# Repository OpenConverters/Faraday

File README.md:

# Faraday

**Automated EMC design review for PCB layouts — in your browser, your board never leaves your machine.**

Faraday loads a PCB layout, screens the whole board with computational geometry + closed-form
transmission-line physics, and returns a **ranked list of crosstalk and EMC risk findings** —
each with the mechanism, the number, a stated confidence tier, and a remediation hint.

## Guided and advanced

One switch in the header, and it is the same review either way — same engine, same
findings, same ranking. **Guided** says each finding in the language of the person who
drew the board (*"this track crosses a gap in the copper underneath it, so its return
current has to detour"* · *"route around the gap, close it, or bridge it with a
capacitor"*), replaces the emissions sliders with four converter presets whose
assumptions are printed rather than hidden, and answers in words. **Advanced** is
everything: decibels, frequencies, confidence tiers, the physics text and the sliders
that drive it. Nothing is suppressed in guided and nothing is softened — the vocabulary
is the only difference, and every number is one click away (panels carry the switch too,
since the header sits behind them). A first visit lands in guided; the choice is
remembered.

## Formats

| Format | Reaches | Notes |
|---|---|---|
| **KiCad** `.kicad_pcb` | KiCad 5–9 | legacy layer names, `(module)`, zone-inherited fills |
| **HyperLynx** `.hyp` | Altium, PADS, Expedition, Eagle | carries its own stackup with permittivity |
| **IPC-2581** `.xml` | rev B/C exporters | no other open-source reader exists |
| **ODB++** job | Altium, Cadence, Mentor, KiCad 9 | exact nets, refdes and values; a directory or one zip |
| **Gerber X2** set | anything that fabs | net attributes where present; all files or one zip |
| **Gerber + IPC-D-356** | Altium fab outputs, TI EVM/TIDA zips | classic RS-274X named by Protel extensions; the .ipc netlist supplies exact nets, refdes and pins, propagated through the copper |

Format is detected from the file's **contents**, not its name. Native CAD
databases are not read — an Altium `.PcbDoc` is a binary OLE file; export
ODB++ (or Gerber X2) from it and drop that. Neither carries a dielectric, so
Faraday reads the layer count off the board and asks only what it is built on.

## Rules

`coupled-run` (edge, broadside, and to copper-pour boundaries) · `diff-pair` (intentional
coupling, never a defect) · `3w` · `plane-crossing` and `sparse-reference` (return-path breaks,
rolled up when systemic) · `via-stub` and `dangling-stub` (λ/4 resonators) ·
`decoupling-distance` · and for power converters, `switch-node` and **`commutation-loop`** —
the input-cap → switch-pair → return loop whose enclosed area dominates converter emissions.
Six rules implement Franz (*EMV: Störungssicherer Aufbau elektronischer Schaltungen*, 5th ed.):
`connector-ground-spread` (scattered cable-ground entries drive the cables as antennas, §7.2),
`plane-cavity-mode` (VCC/GND cavity resonances from Gl. 5.3, corner vs. centre excitation, §5.9.3),
`cap-via-stub` (decoupling-branch stub inductance, §5.6), `critical-mesh-ground` (the
commutation loop crossing a ground-domain boundary, §8.17.1 — via his Stromumschaltanalyse on
the netlist derived from the layout), `pdn-antiresonance` (mixed-value decoupling's parallel
resonance, computed from the PDN branch model, §5.5/§5.9.5) and `edge-radiation`
(switch-node copper at the board edge).

A recognised **line filter** gets its own three: `filter-io-coupling` (the dirty and
clean sides routed together — a path *around* the filter that caps its insertion loss no
matter what the parts do), `y-cap-return` (the Y capacitor's own mounting inductance, and
the frequency above which it stops being a capacitor) and `filter-bypass` (switching
copper beside the connector side, re-injecting behind the filter). The block is found by
shape — a four-pad wound part whose pads split two-and-two into four distinct non-return
nets, with at least one X or Y capacitor on them — so a flyback transformer is never
mistaken for a filter.

**Immunity** is one mechanism, and it is pure layout: `esd-clamp-distance` and
`esd-clamp-return` turn the copper between a connector pin and its clamp — and the clamp's
own path to the plane — into the volts they actually are (`V = L·di/dt`, ~30 A/ns for an
IEC 61000-4-2 contact discharge, ~0.8 nH/mm), and `esd-unprotected-pin` states, at info
grade, which connector pins reach silicon with no clamp near them. Whether a pin needs one
is a product decision, so that last one is coverage, never a verdict. Pads carry their pin names through every importer,
so conduction paths are derivable, not guessed.

The derived meshes are validated against a real-board corpus — vendor-documented EVM hot
loops, human-reviewed member sets, format-determinism pins. The full ledger (stats,
wrong-member cases found and fixed, format coverage) lives in
[corpus/README.md](corpus/README.md).

Monolithic converters (switcher IC + inductor, no discrete FET) surface as **candidate**
switch nodes: the evidence is shown in the meta strip and one click screens the net
(recorded as user-declared in the report). They are never screened automatically, because a
linear regulator followed by an LC filter presents the identical external netlist — measured,
not assumed. A net with a capacitor straight to the return is never a switch node at all:
the cap would short the switch every cycle.

Faraday is an automated **design review**, not compliance prediction. Screening-tier numbers are
first-order estimates for *ranking* risk; a field-solver tier (OMFEM 2D cross-section RLGC +
in-process ngspice via Kirchhoff) refines selected pairs.

## Layout

- `cpp/include/faraday/` — header-only C++20 core (s-expr parser, board IR, KiCad importer,
  transmission-line closed forms, screening engine)
- `cpp/tests/` — Catch2 tests (run the binary directly, never ctest)
- `cpp/tools/` — `faraday_cli`: `.kicad_pcb` → `report.json` + console summary
- `web/` — Vite + Vue GUI: drop a board, rendered layout with severity overlays, hover tooltips,
  two-way-linked findings list. The engine runs in WASM — nothing is uploaded.
- `scripts/build_wasm.sh` — emsdk build of the WASM engine into `web/public/`

## Build (native)

```sh
cmake -S cpp -B build -DCMAKE_BUILD_TYPE=Release
cmake --build build -j
./build/test_faraday        # Catch2 (run the binary directly, never ctest)
./build/faraday_cli board.kicad_pcb -o report.json
./build/faraday_cli board.hyp
./build/faraday_cli board.xml --stackup default-4layer
```

## The bench — field solve and transient, in the browser

Any coupled-run finding offers **Solve this cross-section**. That opens a 2D
boundary-element extraction of the actual geometry and a transient of the coupled pair,
both running in the page:

- the **field** of the real cross-section, computed in closed form from the panel charges
  (no mesh, and the reference plane is exact by images rather than truncated);
- **RLGC** — Z₀, Z even/odd, ε_eff, delay, mutual L and C, backward coupling;
- the **victim's noise waveform**, NEXT and FEXT, against its receiver's threshold;
- a **verdict in millivolts** against the DC input margin of a named logic family, and
  the separation that would bring it back under budget.

Extraction plus transient is a few milliseconds, so the sliders — separation, edge rate,
coupled length, swing — re-solve the physics as they move. See
[docs/browser-field-tier.md](docs/browser-field-tier.md) for the formulation, the
validation table, and the modelling limits.

## Radiated emissions — does it pass?

On a converter, `commutation-loop` findings offer **Predict radiated emissions →**. The
enclosed loop area comes off the copper — the one input every other estimator makes you
measure by hand — and the panel puts the resulting spectrum against the **CISPR 32 /
EN 55032** or **FCC Part 15** limit line, with a margin in dB.

Sliders for switched current, switching frequency, edge rate and duty; the plateau above
the edge knee is set by loop area, current and edge rate alone, so halving any one of
them buys exactly 6 dB.

The same panel carries the **common-mode budget**: how much common-mode current an
attached cable of a given length may carry and still pass. Faraday cannot predict your
actual common-mode current — it comes from ground-plane impedance and return-path
detours, not from geometry — but the inverse needs no unknowns, and it lands in
*microamps*, which is why an ordinary current probe never sees the mechanism that fails
most products.

### Conducted — which mode, at what frequency, and how many dB

Below 30 MHz nothing radiates off a board this size; it walks out on the wires, and it
walks out as **two different problems that need two different components**. The panel
drives the same trapezoid into the two paths a LISN measures — differential mode through
the input capacitor's branch impedance, common mode through the stray capacitance to
earth — and judges **both against the conducted limit line, here**: CISPR 32 / EN 55032
Class A or B mains, quasi-peak or average, the same values Hertz carries and pinned
against them by test. What comes back is the sentence the estimate is worth: *"39 dB over
the limit at 0.5 MHz, and it is common-mode noise"*, with the frequency above which it
stays common mode, and the attenuation each stage has to find at the design frequency
(ANP015's `A_req = level − limit + 10 dB`). A common-mode problem and a differential-mode
problem are fixed by different parts, so which one you have is the first question, not a
footnote.

**The input capacitors are the board's own.** The differential-mode path *is* the input
branch's impedance, and that branch is on the layout: the commutation loop already names
the capacitor that supplies the current step, so its rail is the branch, and every
capacitor across it joins in — with the **mounting inductance measured pad-to-via** on
your copper, not a datasheet ESL. It is carried as a network rather than a lumped value,
because the bulk sets C, the ceramics set L, and their crossover is a real feature of the
curve. (Fixing this found a parser bug worth its own line: `390µF` was being silently
skipped, because the micro sign is not ASCII — three of the five capacitors on the MPPT's
own input rail.)

**Limit lines**: CISPR 32 / EN 55032 mains, Class A and B, quasi-peak and average — and
**CISPR 25** conducted, classes 1–5, for automotive. CISPR 25 only regulates protected
broadcast bands, so between them there is no limit and the verdict says exactly that
instead of scoring against a zero; when the switching fundamental lands in a gap, no
attenuation figure is quoted at all. The DM model is written against the 50 µH/100 Ω mains
network, and against an automotive line the panel says so rather than quietly reading the
wrong LISN.

**C_stray is derived, not invented.** The plate that turns dV/dt into common-mode current
is the switching copper, and Faraday measures it off the layout the same way it measures
the commutation loop — tracks, pads and pours on every switch net, summed. What a layout
file cannot carry is how far the metalwork is, so that is the only thing left to ask:
a gap in millimetres, and whether the board is spaced off the chassis (air) or bolted
against it (through the laminate, 4.5×). Fringing only adds, so the figure is a stated
floor on the geometry's contribution — a heatsink on the device tab, a transformer's
inter-winding capacitance and the harness add paths no layout can see.

**The operating point can come from the design.** Switched current, switching frequency,
edge rate and bus voltage are circuit properties no layout carries — so Faraday takes them
from whatever designed the converter: `#op=<base64 json>` in the URL fragment (the reverse
direction of the Hertz bridge, private for the same reason), range-checked at the door and
credited in the meta strip. Without one, guided mode offers four converter presets and
prints the numbers behind the choice.

Then **design the filter that fixes this →** hands the two mode spectra to
[Hertz](https://hertz.openconverters.com) in the URL *fragment* — the part of a URL that
never reaches any server — where the CM and DM stages get sized against real parts and
the filter's own PCB can be generated. Levels are peak against a quasi-peak line, which
errs pessimistic; DM ±10 dB, CM ±15 dB. It seeds a filter design before hardware exists.
It does not replace a LISN.

The loop figure is an **estimate**, and the panel says so where it cannot be missed: differential-mode
loop radiation only, no common-mode current on attached cables (which dominates most real
failures), no enclosure, no board resonances. A clean result means this loop is not your
problem — not that the product passes.

## The SPICE deck — what the copper adds, where a simulator can read it

A conducted-emissions prediction needs two halves. A circuit simulation knows
the devices and nothing about the copper; Faraday measures the copper and cannot
know the devices. `--spice` writes Faraday's half:

```bash
faraday_cli board.kicad_pcb --stackup default-4layer \
    --spice deck.cir --manifest deck.json --chassis-gap-mm 8
```

The subcircuit is five ports — the rail as it *arrives*, the rail *after* the
mesh inductance (where the switching cell attaches), the switch node, the return
and chassis — and between them the parasitics, each measured: the commutation
mesh's inductance (Grover over the derived loop hull, ~15% against FastHenry),
the input capacitor bank part by part with **mounting inductance measured
pad-to-via**, and the stray capacitance from the dv/dt copper area to a stated
chassis gap. It is topology-neutral on purpose: Faraday measures copper, it does
not decide that a board is a buck.

The manifest gives every value a **provenance** — `measured` off the copper,
`derived` from measured quantities, `stated` by you, or `default` (a model
constant, named as such: ESR is the only one, and for an electrolytic it is
optimistic). A deck whose reader cannot tell which is which gets trusted
uniformly, and most of it should not be.

And the file **names its own absences** at the top, before anything a machine
reads: no device models, no gate loop, no control loop, nothing off the board.
It is deliberately not runnable alone — a deck that omitted those silently would
look runnable and produce numbers with the authority of a simulation and the
content of a guess. `faraday_spice_check` (built when Kirchhoff is available)
wraps it in a harness and solves an operating point through Kirchhoff's
**in-process libngspice**, so "it parses" is a fact and not a hope.

Boards that cannot answer say so: no switch node, no derived commutation loop,
or a stackup that does not fit gets a sentence and an exit code, never an empty
deck. This is stage 1 of ABT #804 — the pipeline that ends in a simulated CM/DM
spectrum judged against a limit line.

## The whole conducted pipeline — a board in, a CM/DM verdict out

The deck above is stage 1 of four (ABT #804). End to end, on your own machine,
nothing uploaded:

```bash
# 1. the device, from the parts catalogue — or a refusal
kelvin-spice-model --catalog mosfets.ndjson --part EPC2019 --name SW --out q.lib

# 2. the board's parasitics + that device + a LISN, run to steady state
faraday_emi_sim board.kicad_pcb --stackup default-4layer --chassis-gap-mm 8 \
    --model q.lib --vin 48 --duty 0.4 --fsw 500e3 --iload 10 --out emi.json

# 3. read it the way a receiver does, and judge it
python3 hertz/scripts/read_simulated.py emi.json --limit cispr32b --out spectra.json
```

```
 DM  worst   -32.3 dB at   2.000 MHz   (level 88.3 dBuV, needs 42 dB …)
 CM  worst    -3.6 dB at   2.000 MHz   (level 59.6 dBuV, needs 14 dB …)
dominant   : DM — that is the stage to design first
```

Each repo owns its half: **Kelvin** the device model and its *tier* (vendor /
datasheet-parameterised / refused — never a class default, which is
indistinguishable from a real model once it is in a netlist), **Faraday** the
parasitics and the assembly, **Kirchhoff** the in-process libngspice, **Hertz**
the LISN, the CM/DM separation and the limit lines. Nothing is duplicated.

`spectra.json` loads straight back into the emissions panel, where the
simulated curves are drawn **beside** the analytic trapezoid seed rather than
replacing it, with the gap between them stated at the seed's worst frequency.
On the MPPT the two independent paths ask for 14 dB of CM attenuation each and
42 vs 50 dB of DM — inside the seed's own ±10 dB band, which is the first
evidence either path has that the other is not wrong.

What it still is not: **validated**. A simulated spectrum with a limit line on
it looks like a compliance prediction, and this project earns those claims
(FastHenry for loop inductance, vendor hot loops for the derived mesh, nine
boards for cross-format agreement). ABT #810 is that instrument —
`hertz/scripts/compare_measured.py` reports the error per decade against a real
LISN measurement — and it is open, waiting on lab data rather than on code.

## The return-path layer

The **return path** chip colours every trace by its *effective loop height* — how far
away its return current really is, in millimetres. The regime is high frequency, where
the return concentrates directly under the trace: the dielectric height where the plane
is genuinely there (checked against the actual pour polygons), the lateral detour around
a slot edge where it is not, and the hop to the nearest spanning stitching via at every
layer change.

Every number in this layer is a **geometric fact of the layout** — no assumed currents,
no field units, no dB. It replaced a "radiation attribution" whose ranking turned out to
be 97% a restatement of the switch-node rule once measured; the defensible far-field
number lives in the emissions panel, which has a limit line to check it against.

## The component near-field map

The **near field** chip opens a different regime from the radiation layer. At component
scale below ~1 GHz, `k·r ≪ 1` and the fields *are* the magnetostatic dipole fields:
decay is **1/r³ — 18 dB per doubling**, not 6, and E and H are independent (wave
impedance spans five orders of magnitude at 5 mm, so the far-field `+51.5 dB` conversion
is wrong by ±40–55 dB there).

It shows |H| in A/m at a stated probe height, and for each sensitive component the
voltage induced in its own loop against the threshold for its class — a precision
current-sense amp is judged at 15 µV, a 12-bit ADC at 806 µV.

**This is why some components get shielded**, and the answer has two halves that are
routinely conflated. A thin conductive can is excellent against a *voltage-driven*
E-field source (reflection dominates; the bond to ground is the limit, not the metal)
and **nearly useless against a low-frequency magnetic near field** — single-digit dB
below ~10 MHz regardless of material. A magnetically shielded inductor is not shielded
by a can at all; it has a closed magnetic path.

It renders as a heat wash **on the board itself**, with the copper drawn over it, and
**victims & shielding →** opens the per-part table plus a shield-can model. That model
shows the thing a datasheet usually hides: at 130 MHz a 0.2 mm wall absorbs ~950 dB and
only the **cover-to-frame contact pitch** matters, while at 500 kHz the wall binds
instead and tin-plated steel beats brass by ~49 dB. Same can, opposite lever.

It carries no dBµV/m, no limit line and no pass/fail: there is no reliable near-field to
far-field transform. See [docs/near-field-map-design.md](docs/near-field-map-design.md).

## The parts — click one, read the datasheet, get a cross-reference

Every component is drawn on the board as a body over its pads (the IR carries no
courtyard, so a part is a black box in the literal sense: the union of its pads and
a margin), with its reference on it once there is room. The **parts** chip turns the
layer off. Hovering says reference, value, footprint, pin count and side; **clicking
opens the part inspector**, which is what a PCB explorer shows and then what only this
one can:

- **On the board**: every pin and the net it is on, the layer, the placement, and the
  review's findings that touch the part's nets — one click jumps to the finding.
- **In the catalogue** — [Kelvin](https://kelvin.openconverters.com), the OpenConverters
  parts librarian, read *in the browser* (same-origin shards, one record per HTTP Range
  read; the board never leaves the machine). A part number on the board is looked up as
  an exact string, and the inspector says which catalogue families it searched and
  whether the hit was exact or a substring. The record comes back with the
  manufacturer's own **datasheet link**, the headline specs, every curve the datasheet
  carries, and the flattened spec sheet. When the export carried a part number and no
  value (Altium's ODB++), the record's value can be **adopted onto the board** in one
  click, so the PDN and the conducted models get the capacitance they refuse to guess.
- **No part number?** A KiCad board says `100n` in a `C_0603` — a value, not a part. The
  inspector matches the value (inside an E-series step) and the package read off the
  footprint name against the catalogue and lists what fits, stating how many value
  matches it scanned, how many carry no case code, and how many sit in another package.
  Pick one and it becomes the original for the record and the cross-reference.
- **Cross-references**: Kelvin's own deterministic ranker (the C++ `CrossRef` behind
  kelvin.openconverters.com, imported from the sibling checkout — never a second
  implementation) scores every candidate from the manufacturers you mark against the
  original's datasheet numbers: per-parameter pass/warn/fail, a grade (drop-in · minor
  review · major review · redesign · no substitute), the direction (upgrade/downgrade),
  physical fit, mount type, AEC-Q grade and lifecycle. Default question: *any other
  manufacturer*. When the original's own gating parameter is not in the catalogue, no
  candidate can grade better than partial, and the table says so.

A refdes prefix is a convention, not a contract — ANSI, DIN and IEC disagree on what
`T`, `Q` and `L` mean — so prefixes only *order* the families searched; the footprint
name and the value's unit letter weigh in first, and the remaining families are one
click away with the download cost stated. A verdict is a catalogue comparison, not a
qualification: read both datasheets.

**Does it fit? The measured body answers, not the case string.** A catalogue case code
is genuinely ambiguous and vendors disagree: Murata ships 1.0 × 0.5 mm capacitors whose
case field reads `0603` — the *metric* code for what everyone else calls an imperial
0402. Read as an imperial code that part gets offered as fitting a 1.6 mm land it is
0.6 mm too short for. So where a record carries a mechanical drawing, the part's own
length and width decide the fit (orientation-agnostic, ±12% per axis, which is wide
enough for a real 0603 body at 1.60 ±0.15 and narrow enough that neighbours stay
distinct on both axes); the case code answers only where no drawing exists, and the
panel says which one spoke. Non-chip packages (TO-220, SOT-23, a can) keep the code
check: those are families of drawings with real variation, not one standard rectangle.

### The catalogue overlay — which of these parts can I actually source?

The **in catalogue** chip asks the catalogue about *every* part on the board at once
and recolours the parts layer by the answer: green identified by part number, amber
candidates to choose from, red nothing in the catalogue fits, and grey **the board never
named it** — a part the export described with neither a number nor a value, which is a
gap in the export and not a hole in the catalogue, so it gets its own colour rather than
being counted as a miss. Work is grouped by catalogue family so each family downloads
once, progress is reported as it goes, and a second click stops it and keeps what was
answered. On the MPPT demo board: 139 parts, 2 identified, 91 with candidates, 33
unmatched, 13 the board never named.

### When the catalogue has never heard of it

A part number the catalogue cannot resolve is a dead end the inspector can get out of:
**look it up at the distributor** hands the part number to
[Heaviside](https://heaviside.openconverters.com)'s librarian, which searches the
distributor, converts the result into the same catalogue record shape, schema-validates
it, and **stages it for the catalogue**. What comes back renders with exactly the code
that renders a catalogue record — the vendor's datasheet link, the specs, the curves.

Three outcomes, kept distinct on purpose, because a caller acts on them: the part was
found and staged; the distributor answered and has no such part; or **the distributor
could not be asked** (credentials, transport, rate limit). The third is never dressed as
the second — a reader told "this part does not exist" would go and enter it by hand.

Nothing here writes to the catalogue. A found part lands in Heaviside's `staging/`, a
librarian applies it into TAS, and the next index build is what puts it in front of you.
A web button is not a way around that review. Only the part *number* leaves the browser;
it is a public string printed on the component, and the layout stays where it always
was.

Serving: the engine (`/kelvin.js`) and the data set (`/kelvin/*`) are same-origin — the
CSP allows nothing else. Prod nginx serves Kelvin's deployed bundle and the box's shared
`/cache/kelvin` (`ops/faraday.nginx`); the dev server proxies both from the live Kelvin
site, so a local board talks to the real catalogue. Kelvin's web sources are imported at
build time from `../../Kelvin/web/src` (`KELVIN_WEB_SRC` to override).

## PDN impedance — measured off the board

The **pdn** chip turns every decoupling capacitor into a series R-L-C branch whose
inductance is **measured off the layout** — pad-to-via escape on each terminal plus the
barrels — and plots the rail's |Z| against a target derived from your transient current
and allowed ripple, with its anti-resonance peaks marked. A cap whose mounting
inductance exceeds its ESL is wasted by placement, not by choice of part, and this is
the view that shows it.

## Also in the box

- **Impedance calculator** (from the start screen, no board needed): a real 2D
  boundary-element solve of the cross-section — Z₀, Z_diff, ε_eff, delay — plus a width
  finder that bisects to a target impedance.
- **Report export**: one self-contained HTML file of the whole review, with the
  screening caveats attached to it rather than left behind.
- **Bench sweep**: peak victim noise against separation as a curve, with the budget
  line, not one point at a time.
- **Copper loss**: the bench's transient now carries skin-effect R at the edge's knee
  frequency, so unterminated ringing is damped the amount real copper damps it.
- **Diff-pair skew**: recognized pairs are checked for intra-pair length mismatch —
  skew converts differential signal into the common mode that reaches the cable.
- Near-field victims carry a **cos θ from their own routed direction**, capacitive
  broadside overlaps over switch copper get their divider-ceiling bound, and inductors
  on switch nets are sources with a stated construction derating.

## Formats — what is and is not supported

| format | status |
|---|---|
| KiCad `.kicad_pcb` (v5–v9) | ✅ full |
| HyperLynx `.hyp` | ✅ full |
| IPC-2581 `.xml` | ✅ full |
| Gerber X2 set + Excellon | ✅ full — drop all files (or one zip); needs X2 `%TO.N` net attributes (KiCad's default), because plain RS-274X carries **no netlist** and a netless board would make most rules meaningless. Through vias only; clear-polarity objects are skipped and counted |
| ODB++ | ✅ full — drop the job as one zip (or point the CLI at the directory); needs `eda/data` in the export, which is where the netlist lives. Nets, component values, via spans are exact. Surface holes skipped and counted |
| Altium / Eagle | export **ODB++** or IPC-2581 from those tools and load that |

Detection is by content, not extension.

## Glossary & dismissing findings

The **glossary** button above the findings list explains every rule — what it detects,
the physics, the fix, and what its confidence label really means. Rules can be hidden
by type from the glossary or the filter chips, and any single finding can be dismissed
with its ✕ (per review, restorable in one click).

## Integrations

- **KiCad plugin** (`integrations/kicad/`): a "Review in Faraday" button that serves the
  open board from localhost and loads it via `#load=` — nothing is uploaded. PCM-format
  zip included; official PCM submission is an external review step.
- **GitHub Action** (`integrations/github-action/`): screen a board on every push,
  `--fail-on high|medium` gates the build (exit 3), report JSON as an artifact.
- **`#load=<url>`**: load any board by URL, CORS permitting — the fetch happens in your
  browser.

## Revision diff — "did this change make EMC worse?"

With a board loaded, **compare rev…** takes the previous revision (a board file,
or a report exported earlier) and answers in one line: N new · M worsened ·
K resolved — verdict. Findings are matched by identity (rule + net names +
layers), never by report order, and thresholds separate signal from noise
(a 0.2 dB re-route wiggle is not a regression; +1 dB is). Rows wear NEW/WORSE
badges and *only changes* narrows the list to the delta.

The same diff gates CI: `faraday_cli board.kicad_pcb --baseline old-report.json
--fail-on-regression high|medium` exits 3 only on NEW or WORSENED findings — the
gate a brownfield board can adopt today, without first fixing every legacy
finding.

## Fix generation — stitching vias (v1)

When the return-path layer flags **unstitched layer changes** on a KiCad board,
*generate stitching vias → new file* emits a patched `.kicad_pcb` — the original
is never touched. Every proposed via must land where the reference pour covers
**two** copper layers, clear all foreign copper (pad + 0.2 mm), and it copies
the board's own most common reference-via style — no invented pad/drill sizes.
The generator re-imports its own output and refuses to emit anything
unverified; the unit test additionally demands the fix is never a regression
under the report diff. Boards where no stitch is physically possible (single
reference plane, no via style to copy) get the honest reason instead of a file.
CLI: `--fix-stitching out.kicad_pcb`.

## Custom stackups

The stackup select (or the "no stackup" card) opens an editor: copper count,
copper weight, and per-dielectric height + ε<sub>r</sub> straight off the fab's
stackup drawing, with a live cross-section. Every Z₀, coupling and return-path
figure stands on these numbers — a Gerber set or ODB++ job analysed on a
default preset becomes accurate the moment the real stackup goes in. Entered
stackups are remembered per board file (locally, like everything else) and the
CLI takes the same thing as `--stackup mystackup.json`. Validation is strict:
alternating copper/dielectric, positive thicknesses, ε<sub>r</sub> ≥ 1 on every
dielectric — anything else is refused with the reason, never repaired.

## Stackup policy

Z₀ and coupling depend on the stackup. If the board file carries none, Faraday never assumes one
*silently*. The CLI with no `--stackup` refuses, naming the copper count. `--stackup auto` (the
default of the MCP `review_board` tool, and what the web app does when you have not entered one)
screens on the builtin `default-<N>layer` for the N copper layers counted off the board and stamps
the source `assumed:default-<N>layer (N copper layers counted; the file carries no stackup)` —
printed as a WARNING by the CLI, first in the MCP digest and caveat, and as the "assumed stackup"
button in the GUI. An explicit `--stackup default-<N>layer|stackup.json`, or a stackup the file
carries, always wins. Every report states the stackup it used.

## Physics references

Hammerstad–Jensen microstrip synthesis; Cohn symmetric stripline; Johnson & Graham
(*High-Speed Digital Design*) coupling estimate k = 1/(1+(s/h)²) with the saturated-NEXT bound.
The field tier follows Nabors & White's FastCap formulation (IEEE TCAD 1991) in 2D, and
Paul's *Multiconductor Transmission Lines* for L = μ₀ε₀C₀⁻¹ and the backward-coupling
coefficient. Formulas are cited at the point of use and pinned by tests against published
values — including the exact identity L·C = μ₀ε₀ε_r·I, which holds to 2.6e-16.

## License

MIT.

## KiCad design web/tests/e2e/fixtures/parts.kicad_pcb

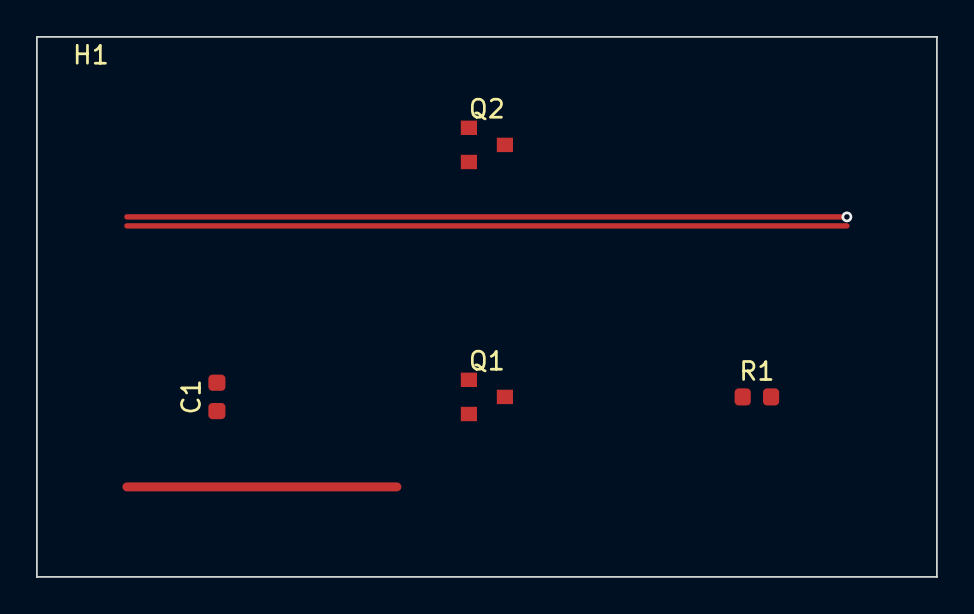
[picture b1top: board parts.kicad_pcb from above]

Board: 2 copper layers, 50.0 x 30.0 mm, 5 parts (0 on the bottom side), 3 nets.

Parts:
C1: 100n; C_0603_1608Metric
H1: MountingHole; MountingHole_3.2mm
Q1: EPC2019; SOT-23
Q2: XYZ9999ABC; SOT-23
R1: 10k; R_0603_1608Metric

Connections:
CLK: C1.1, Q1.1, Q2.1
DATA: Q1.3, Q2.3, R1.1
GND: C1.2, Q1.2, Q2.2, R1.2

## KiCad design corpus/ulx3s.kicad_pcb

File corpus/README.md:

# Corpus validation ledger (Tier 4)

The living record of ABT #422 (closed 2026-08-01; this file is its successor —
update it as boards land). The program: grow the open-source converter corpus,
track (a) the derive success rate of the critical-mesh analysis, (b)
human-reviewed member-set agreement, (c) fallback correctness — and pin every
reviewed board as a Catch2 regression (`test_real_boards.cpp`,
`[corpus-pin]`, SKIP when the corpus is not fetched). Characterization-test
discipline throughout: pins are verified against physical sense and never
silently re-pinned.

## Final stats (2026-08-01)

**Every converter board in the program derives.** 14 derived meshes across 8
physical boards, zero known wrong-member cases:

| Board | Node(s) | Derived mesh | Notes |
|---|---|---|---|
| PoE flyback (Altium ODB++) | NetD17_3 | T7 + D22 + R29 | RCD clamp — includes the D22 a hand-run prototype missed |
| | NetC52_2 | T4 + D21 + R16 | |
| LM5143-Q1EVM (TI gerbers) | ×2 | exact per SNVA-documented hot loops | two-phase buck |
| LM5177EVM (via KiCad 9) | buck + boost | both match SLVAFJ3 | |
| LM5123EVM (via KiCad 9) | boost | closes through the OUTPUT cap | Franz's own example of what pattern-matching gets wrong |
| mppt-2420-lc | SW_NODE | Q1 + Q4 + C4 (71 mm², 25 nH) | pinned |
| mppt-1210-hus | SW_NODE | Q1 + Q4 + C4 (64 mm², 26 nH) | pinned; LOAD_S pinned to keep REFUSING a divider-as-clamp |
| mppt-2420-hc | SW_NODE | Q1 + Q2 + C3 (buck) | TO-220 equal pads → conduction case d (pin 1 = JEDEC control terminal, 2 mm² pad floor) |
| VESC (KiCad + ODB++) | H1/H2/H3 | Q1+Q2+R53+C40 · Q3+Q4+C8 · Q5+Q6+R54+C37 | Kelvin shunts NAMED as mesh members; both formats agree byte-for-byte |

Plus 4 synthetic topology pins in Catch2: buck, boost-with-decoy,
flyback-RCD, Kelvin-shunt bridge — and the determinism pin (pad order +
exporter rounding invariance).

**Correct negatives:** pwm-2420-lus (PWM controller, SOLAR- only), moteus /
FPGA / interface boards, hackrf (pinned: 0 switch nodes, exactly 2
candidates — its dual-LDO + ferrite harness is externally isomorphic to a
fixed buck; see the main README).

**Wrong-member cases found and fixed during the program** (each caught by the
regression pins this ledger mandated — which is the whole argument for them):

- mppt-1210-hus LOAD_S derived a divider (R+R) as a clamp path → two-edge
  clamps must contain a diode; falls back honestly.
- PoE gate-drive SOT-23s with numbered pins hijacked the mesh → 2 mm² pad
  floor on conduction case d.
- mppt-2420-hc SUPPLY_INPUT (L2+Q4 supply-ORing rail) and PoE NetC45_1
  (aux-winding node smoothed by C45) screened as commutation loops → the
  shunt-cap veto: a net with a 2-pad capacitor straight to the return can
  never switch.
- KiCad vs ODB++ of the same VESC picked different caps (C8/277 mm² vs
  C40/221 mm²) and anchor FETs → meshes now scored by pad-hull area (the
  least-inductance loop; C40 was physically right), areas quantized to
  0.1 mm² before ref-name tie-breaks. Centroid-hull scoring was tried and
  REFUTED (mppt-2420-lc's collinear C2 degenerated to ~1 mm²).

## Format coverage — real products on all five formats

- **KiCad**: the corpus (this directory; `scripts/fetch_corpus.py`).
- **Gerber + IPC-D-356**: TI fab exports (TIDA-010979, LM5143-Q1EVM) —
  Altium exporter. Drawing-sheet title blocks are cropped and counted
  (LM5143 screened as 168×105 mm before; really 96×73 with 8.3 m of
  title-block strokes); IPC netting below 95 % of routed copper is reported,
  never silent.
- **ODB++**: the PoE flyback (real Altium product) + VESC through KiCad 9's
  own ODB++ writer — second real exporter, derives identically.
- **HyperLynx**: hyp2mat's Eagle-exported RF filters (hairpinfilter,
  notchfilter; github.com/koendv/hyp2mat) — own stackup honored.
- **IPC-2581**: BeagleBone Black RevB6 (Cadence Allegro, ipc2581.com
  consortium) — screens with an explicit stackup; the file carries no
  permittivity and Faraday refuses to invent one.

Altium native `.PcbDoc` stays refused by design (binary OLE). Altium boards
are covered by three validated routes: ODB++ export, `Gerber_NCdrills_IPC`
fab output, and the `.PcbDoc` → KiCad 9 importer.

## History (ledger entries)

- **2026-07-31 baseline** (9 boards + PoE): derived on mppt-2420-lc and PoE
  flyback; geometric fallback on vesc + mppt-2420-hc (D2PAK role ambiguity).
- **+ conduction cases b/c + SOT-23 refusal pins**: 11 reviewed-correct
  meshes across 7 boards; VESC 1/3 phases.
- **conduction case d + Kelvin-shunt bridge**: every converter board
  derives — 14 meshes across 8 boards; VESC 3/3 with shunts as members.
- **2026-08-01, the "100 %-happy" audit**: pour coverage became a scanline
  UNION (BBB LYR2 175 % → 92.7 %); importer plausibility notes are appended
  by the gate, never overwritten; gerber outlines are the smallest profile
  loop holding ≥95 % of pads+vias; T-junction/pour/mid-via physical-contact
  netting; the shunt-cap veto and monolithic-converter candidates
  (ABT #408/#409/#410); mesh determinism across formats.

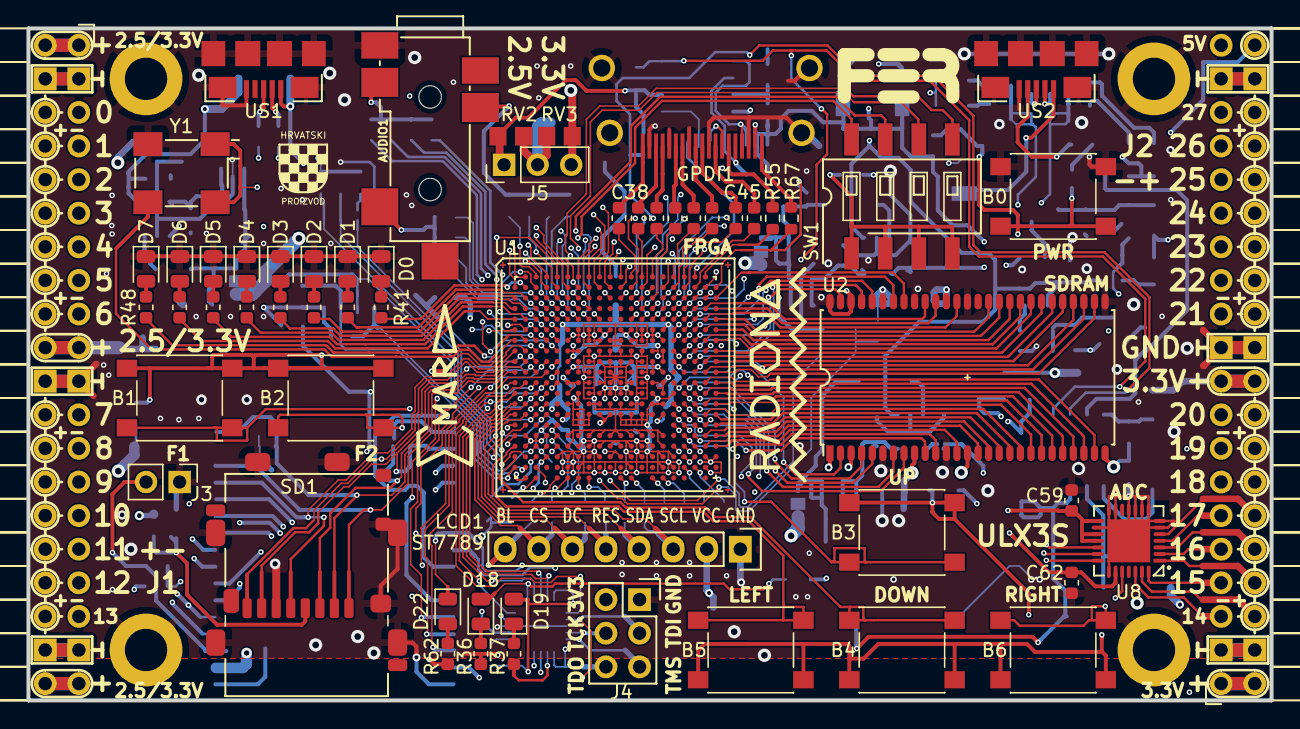
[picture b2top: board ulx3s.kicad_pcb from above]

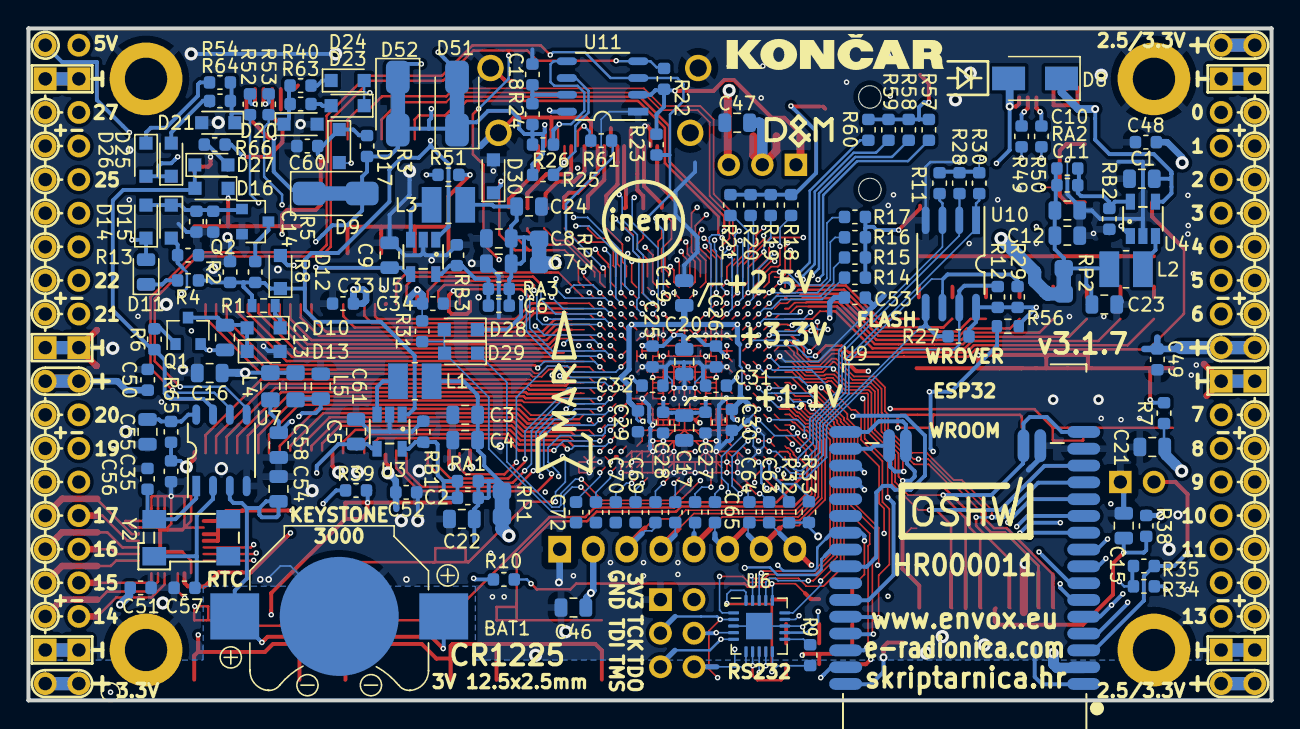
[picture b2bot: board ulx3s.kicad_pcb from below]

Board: 4 copper layers, 94.0 x 50.8 mm, 234 parts (167 on the bottom side), 287 nets.

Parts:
AE1: 433MHz; TestPoint_Pad_D1.0mm
AUDIO1: JACK_TRS_6PINS; CUI_SJ-43516-SMT
B0, B1, B2, B3, B4, B5, B6: PTS645; SW_SPST_PTS645
BAT1: CR1225; Keystone_3000_1x12mm-CoinCell
C1, C3, C4, C5, C7, C8, C9, C11, C12, C15, C21, C54, C55, C58, C61: 22uF; C_0805_2012Metric
C2, C6, C10, C18: 100pF; C_0603_1608Metric
C13, C16, C17, C19, C20, C22, C23, C24, C46, C47: 2.2uF; C_0805_2012Metric
C14, C59, C60, C62: 220nF; C_0603_1608Metric
C25, C26, C27, C28, C29, C30, C31, C32, C33, C34, C35, C38, C39, C40, C41, C42, C43, C44, C45, C48, C49, C50, C51, C52, C53, C63, C64, C65, C66, C67, C68, C69, C70, C71, C72: 22nF; C_0603_1608Metric
C56, C57: 4.7pF; C_0603_1608Metric
D0, D4, D11, D19: RED; LED_0805_2012Metric
D1, D5: ORANGE; LED_0805_2012Metric
D2, D6, D18: GREEN; LED_0805_2012Metric
D3, D7, D22: BLUE; LED_0805_2012Metric
D8: STPS2L40AF; D_SMA
D9, D51, D52: 0; D_SMA_Jumper_NC
D10, D13, D14, D16, D17, D23, D24, D25, D26, D27, D28, D29: 1N914; D_SOD-323_HandSoldering
D12, D15: BAT54W; D_SOD-323_HandSoldering
D20, D21, D30: 3.6V; D_SOD-323_HandSoldering
D&M: dm2mm
EMARD: emard12mm
EMARD#2: emard12mm
GPDI1: GPDI-D; CONN-10029449-111RLF
H1, H2, H3, H4: HOLE; MountingHole_3.2mm_M3_ISO14580_Pad
HR: HR; hrvatski
J1, J2: CONN_02X20; Socket_Strip_Angled_2x20
J3: WIFI_OFF; PinHeader_1x02_P2.54mm_Vertical
J4: CONN_02X03; Socket_Strip_Straight_2x03
J5: VJ1; PinHeader_1x03_P2.54mm_Vertical
L1, L2, L3: 2.2uH; L_1008_1210
L4, L5: 33uH; L_0805_2012Metric_Pad1.15x1.40mm_HandSolder
LCD1: ST7789; st7789
OSHW: OSHW2mm; oshw
Q1: BC857; SOT-23
Q2: 2N7002; SOT-23
R1, R3, R4, R25, R26, R30: 4.7k; R_0603_1608Metric
R2: 18k; R_0603_1608Metric
R5: 2.2M; R_0603_1608Metric
R6, R8, R14, R18, R29, R40, R54, R57, R66: 1.1k; R_0603_1608Metric
R7, R10, R17, R21, R39, R51, R60: 130; R_0603_1608Metric
R9, R13, R31, R32, R33, R34, R56, R63, R64: 15k; R_0603_1608Metric
R11, R12, R27, R28, R55: 10k; R_0603_1608Metric
R15, R19, R35, R36, R37, R41, R42, R43, R44, R45, R46, R47, R48, R58, R61, R62, R65, R67: 549; R_0603_1608Metric
R16, R20, R59: 270; R_0603_1608Metric
R22, R23: 3.3k; R_0603_1608Metric
R24: 100k; R_0603_1608Metric
R38: 0.47; R_0603_1608Metric
R49, R50, R52, R53: 27; R_0603_1608Metric
RA1, RA2, RA3: 15k; R_0603_1608Metric
RB1: 18k; R_0603_1608Metric
RB2: 4.7k; R_0603_1608Metric
RB3: 3.3k; R_0603_1608Metric
RP1, RP2, RP3: 0; R_0805_2012Metric_Pad1.29x1.40mm_HandSolder_Jumper_NC
RV2, RV3: 0; R_0805_2012Metric_Pad1.29x1.40mm_HandSolder
SD1: 104031-0811; SCHD3A100-104031-0811
SW1: SW_DIP_x04; SW_DIP_x4_W8.61mm_Slide_LowProfile
U1: LFE5U-85F-6BG381C; BGA-381_pitch0.8mm_dia0.4mm
U2: MT48LC16M16A2TG; TSOP54
U3, U4, U5: TLV62569DBV; TSOT-25
U6: FT231XQ; FT231X-QFN-20-1EP_4x4mm_P0.5mm_EP2x2mm
U7: MCP7940NT; SOT96-1
U8: MAX11125; MAX1112x-TQFN-28-1EP_5x5mm_Pitch0.5mm
U9: ESP32
U10: IS25LP128F-JBLE; SOA008-150-208mil
U11: PCA9306D; SM8
US1, US2: MICRO_USB; USB-MICRO-B-FCI-10118192-0001LF
Y1: FNETHE025; Crystal_SMD_7050_4Pads
Y2: 32768Hz; Crystal_SMD_ABS07
fer: fer; fer4mm6
koncar: koncar
radiona: radiona

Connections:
2V5_3V3: C26.1, C47.1, C48.1, C49.1, C53.1, J1.1, J1.2, J1.19, J1.20, J1.39, J1.40, J5.2, R51.1, RV2.2, RV3.1, U1.F9, U1.F10, U1.H6, U1.H7, U1.J6
+1V1: C17.1, C27.1, C28.1, RP1.2, U1.H8, U1.H9, U1.H10, U1.H11, U1.H12, U1.H13, U1.J8, U1.J13, U1.K8, U1.K13, U1.L8, U1.L13, U1.M8, U1.M13, U1.N8, U1.N9, U1.N10, U1.N11, U1.N12, U1.N13, U1.T6, U1.T7, U1.T8, U1.T9, U1.T10, U1.T11, U1.T12, U1.T13, U1.T14, U1.T15, U1.U6, U1.U15
+2V5: C19.1, C29.1, C30.1, J5.1, R22.1, R23.1, RP2.2, RV2.1, U1.F6, U1.F15, U1.P6, U1.P15, U1.V10, U1.V11, U1.V17, U1.V18, U11.2
+3V3: C16.1, C20.1, C21.1, C25.1, C31.1, C32.1, C33.1, C34.1, C35.1, C46.1, C50.1, C51.1, C52.1, D11.2, D14.1, J2.1, J2.2, J2.19, J2.20, J4.2, J5.3, L4.1, L5.1, LCD1.2, R7.1, R11.1, R12.1, R27.1, R28.1, R29.1, R30.1, R31.1, R32.1, R33.1, R34.1, R38.2, R39.1, R56.1, R62.2, R65.1, RP3.2, RV3.2, U1.F11, U1.F12, U1.H14, U1.H15, U1.J15, U1.L6, U1.L7, U1.L14, U1.L15, U1.M6, U1.M15, U1.P9, U1.P10, U1.T2, U1.T3, U1.T4, U1.U2, U2.1, U2.3, U2.9, U2.14, U2.27, U2.43, U2.49, U9.2, U10.8, U11.8, Y1.1, Y1.4
+5V: C1.1, C5.1, C9.1, C13.1, D8.1, D9.2, D51.1, D52.2, GPDI1.18, Q1.2, R3.1, R24.1, R25.1, R26.1, U3.4, U4.4, U5.4
/analog/ADC3V3: C58.1, C59.1, L4.2, U8.15, U8.17, U8.18
/analog/ADCD3V3: C61.1, C62.1, L5.2, U8.23
/analog/AUDIO_L: AUDIO1.2, R14.2, R15.2, R16.2, R17.2
/analog/AUDIO_R: AUDIO1.3, R18.2, R19.2, R20.2, R21.2
/analog/AUDIO_V: AUDIO1.4, R57.2, R58.2, R59.2, R60.2
/blinkey/ALED0: D0.2, R41.2
/blinkey/ALED1: D1.2, R42.2
/blinkey/ALED2: D2.2, R43.2
/blinkey/ALED3: D3.2, R44.2
/blinkey/ALED4: D4.2, R45.2
/blinkey/ALED5: D5.2, R46.2
/blinkey/ALED6: D6.2, R47.2
/blinkey/ALED7: D7.2, R48.2
/blinkey/BTNPUL: B1.1, B2.1, R7.2
/blinkey/BTNPUR: B3.1, B4.1, B5.1, B6.1, R39.2
/blinkey/LED_PWREN: D18.1, R36.1
/blinkey/LED_TXLED: D19.1, R37.2
/blinkey/LED_WIFI: D22.2, R62.1
/blinkey/SWPU: R51.2, SW1.1, SW1.2, SW1.3, SW1.4
/flash/FLASH_MISO: R28.2, U1.V2, U10.2
/flash/FLASH_MOSI: R27.2, U1.W2, U10.5
/flash/FLASH_SCK: R29.2, U1.U3, U10.6
/flash/FLASH_nCS: R30.2, U1.R2, U10.1
/flash/FLASH_nHOLD: R12.2, U1.W1, U10.7
/flash/FLASH_nWP: R11.2, U1.Y2, U10.3
/flash/FPGA_DONE: R32.2, U1.Y3
/flash/FPGA_INITN: R33.2, U1.V3
/flash/FPGA_PROGRAMN: D28.2, D29.2, R31.2, U1.W3
/gpdi/GPDI_CEC: GPDI1.13, R61.1
/gpdi/GPDI_CLK+: C44.2, GPDI1.10
/gpdi/GPDI_CLK-: C45.2, GPDI1.12
/gpdi/GPDI_D0+: C42.2, GPDI1.7
/gpdi/GPDI_D0-: C43.2, GPDI1.9
/gpdi/GPDI_D1+: C40.2, GPDI1.4
/gpdi/GPDI_D1-: C41.2, GPDI1.6
/gpdi/GPDI_D2+: C38.2, GPDI1.1
/gpdi/GPDI_D2-: C39.2, GPDI1.3
/gpdi/GPDI_HPD: GPDI1.19, R67.2
/gpdi/GPDI_UTIL: GPDI1.14, R55.2
/gpdi/VREF2: C18.1, R24.2, U11.7
/gpio/IN5V: D51.2, J2.39
/gpio/OUT5V: D52.1, J2.40
/power/FB1: C2.2, RA1.2, RB1.2, U3.5
/power/FB2: C10.2, RA2.2, RB2.2, U4.5
/power/FB3: C6.2, RA3.2, RB3.2, U5.5
/power/FTDI_nSUSPEND: D12.2, R10.1
/power/HOLD: D11.1, R4.1
/power/L1: L1.1, U3.3
/power/L2: L2.1, U4.3
/power/L3: L3.1, U5.3
/power/OSCI_32k: C56.2, U7.1, Y2.4
/power/OSCO_32k: C57.2, U7.2, Y2.1
/power/P1V1: C2.1, C3.1, C4.1, C22.1, L1.2, RA1.1, RP1.1
/power/P2V5: C10.1, C11.1, C12.1, C23.1, L2.2, RA2.1, RP2.1
/power/P3V3: C6.1, C7.1, C8.1, C24.1, L3.2, RA3.1, RP3.1
/power/PWREN: D12.1, R1.2, R2.1, R4.2, R8.1, U3.1, U4.1, U5.1
/power/RTCVDD: C55.1, R65.2, U7.8
/power/SHD: Q2.3, R8.2
/power/SHUT: C14.1, D14.2, D15.1, Q2.1, R5.1
/power/VBAT: BAT1.1, C54.1, U7.3
/power/WAKE: D10.1, R1.1
/power/WAKEUPn: D16.2, D27.1, R6.2, U7.7
/power/WKUP: C13.2, D10.2, D13.1, Q1.3
/power/WKn: Q1.1, R6.1
/serdes/SRCLKN: C68.1, U1.Y12
/serdes/SRCLKP: C67.2, U1.Y11
/serdes/SRXN00: C64.1, U1.Y6
/serdes/SRXN01: C66.1, U1.Y8
/serdes/SRXN10: C70.1, U1.Y15
/serdes/SRXP00: C63.2, U1.Y5
/serdes/SRXP01: C65.2, U1.Y7
/serdes/SRXP10: C69.2, U1.Y14
/serdes/STXN11: C72.1, U1.W18
/serdes/STXP11: C71.2, U1.W17
/usb/ANT_433MHz: AE1.1, U1.G1
/usb/FPD+: R53.2, US2.3
/usb/FPD-: R52.2, US2.2
/usb/FTD+: R50.2, US1.3
/usb/FTD-: R49.2, US1.2
/usb/US2VBUS: D9.1, US2.1
/wifi/SD3V3: C15.1, R38.1, SD1.4
/wifi/WIFIEN: J3.2, R35.2, U9.3
ADC_CSn: U1.R17, U8.20
ADC_MISO: U1.U16, U8.24
ADC_MOSI: U1.R16, U8.21
ADC_SCLK: U1.P17, U8.19
AUDIO_L0: R14.1, U1.E4
AUDIO_L1: R15.1, U1.D3
AUDIO_L2: R16.1, U1.C3
AUDIO_L3: R17.1, U1.B3
AUDIO_R0: R18.1, U1.A3
AUDIO_R1: R19.1, U1.B5
AUDIO_R2: R20.1, U1.D5
AUDIO_R3: R21.1, U1.C5
AUDIO_V0: R57.1, U1.H5
AUDIO_V1: R58.1, U1.F2
AUDIO_V2: R59.1, U1.F5
AUDIO_V3: R60.1, U1.E5
BTN_D: B4.2, U1.V1
BTN_F1: B1.2, U1.R1
BTN_F2: B2.2, U1.T1
BTN_L: B5.2, U1.U1
BTN_PWRn: D17.2, U1.D6
BTN_R: B6.2, U1.H16
BTN_U: B3.2, U1.R18
CLK_25MHz: U1.G2, Y1.3
FPDI_CEC: R61.2, U1.A18
FPDI_CLK+: C44.1, U1.A17
FPDI_CLK-: C45.1, U1.B18
FPDI_D0+: C42.1, U1.A16
FPDI_D0-: C43.1, U1.B16
FPDI_D1+: C40.1, U1.A14
FPDI_D1-: C41.1, U1.C14
FPDI_D2+: C38.1, U1.A12
FPDI_D2-: C39.1, U1.A13
FPDI_HPD: D30.1, R67.1, U1.B20
FPDI_SCL: R23.2, U1.E12, U7.6, U11.3
FPDI_SDA: R22.2, U1.B19, U7.5, U11.4
FPDI_UTIL: R55.1, U1.A19
FT2V5: D19.2, R9.2, U6.10, U6.20
FTDI_RXD: U1.L4, U6.1
FTDI_TXD: U1.M1, U6.17
FTDI_TXDEN: U1.L3, U6.15
FTDI_nDTR: U1.N1, U6.18
FTDI_nRTS: U1.M3, U6.19
FTDI_nRXLED: U1.L5, U6.14
FTDI_nSLEEP: D18.2, R10.2, U6.16
FTDI_nTXLED: R37.1, U6.7
GN0: J1.5, U1.C11
GN1: J1.7, U1.A11
GN2: J1.9, U1.B10
GN3: J1.11, U1.C10
GN4: J1.13, U1.A8
GN5: J1.15, U1.B8
GN6: J1.17, U1.C7
GN7: J1.23, U1.B6
GN8: J1.25, U1.A5
GN9: J1.27, U1.B1
GN10: J1.29, U1.B4
GN11: J1.31, U1.E3
GN12: J1.33, U1.F3, U9.8
GN13: J1.35, U1.G5, U9.5
GN14: J2.5, U1.U17, U8.26
GN15: J2.7, U1.P16, U8.28
GN16: J2.9, U1.M17, U8.2
GN17: J2.11, U1.L17, U8.4
GN18: J2.13, U1.H17
GN19: J2.15, U1.G18
GN20: J2.17, U1.E17
GN21: J2.23, U1.D17
GN22: J2.25, U1.C15
GN23: J2.27, U1.C17
GN24: J2.29, U1.D16
GN25: J2.31, U1.E14
GN26: J2.33, U1.C13
GN27: J2.35, U1.E13
GND: AUDIO1.1, B0.2, BAT1.2, C1.2, C3.2, C4.2, C5.2, C7.2, C8.2, C9.2, C11.2, C12.2, C14.2, C15.2, C16.2, C17.2, C18.2, C19.2, C20.2, C21.2, C22.2, C23.2, C24.2, C25.2, C26.2, C27.2, C28.2, C29.2, C30.2, C31.2, C32.2, C33.2, C34.2, C35.2, C46.2, C47.2, C48.2, C49.2, C50.2, C51.2, C52.2, C53.2, C54.2, C55.2, C56.1, C57.1, C58.2, C59.2, C60.2, C61.2, C62.2, D0.1, D1.1, D2.1, D3.1, D4.1, D5.1, D6.1, D7.1, D13.2, D20.2, D21.2, D30.2, GPDI1.0, GPDI1.2, GPDI1.5, GPDI1.8, GPDI1.11, GPDI1.17, H1.1, H2.1, H3.1, H4.1, J1.3, J1.4, J1.21, J1.22, J1.37, J1.38, J2.3, J2.4, J2.21, J2.22, J2.37, J2.38, J3.1, J4.1, LCD1.1, Q2.2, R2.2, R5.2, R13.2, R36.2, RB1.1, RB2.1, RB3.1, SD1.6, SD1.GM1, SD1.GM2, SD1.GM3, SD1.GM4, SD1.GS1, SD1.GS2, SD1.GS3, SD1.GS4, U1.B7, U1.B14, U1.C19, U1.D4, U1.F7, U1.F8, U1.F13, U1.F14, U1.G4, U1.G6, U1.G7, U1.G8, U1.G9, U1.G10, U1.G11, U1.G12, U1.G13, U1.G14, U1.G15, U1.G17, U1.H19, U1.J2, U1.J7, U1.J9, U1.J10, U1.J11, U1.J12, U1.J14, U1.K6, U1.K7, U1.K9, U1.K10, U1.K11, U1.K12, U1.K14, U1.K15, U1.L9, U1.L10, U1.L11, U1.L12, U1.M2, U1.M7, U1.M9, U1.M10, U1.M11, U1.M12, U1.M14, U1.M16, U1.N6, U1.N7, U1.N14, U1.N15, U1.P7, U1.P8, U1.P11, U1.P12, U1.P13, U1.P14, U1.R4, U1.R19, U1.U4, U1.U7, U1.U8, U1.U9, U1.U10, U1.U11, U1.U12, U1.U13, U1.U14, U1.V5, U1.V6, U1.V7, U1.V8, U1.V9, U1.V12, U1.V13, U1.V14, U1.V15, U1.V16, U1.V19, U1.V20, U1.W6, U1.W7, U1.W12, U1.W15, U1.W16, U1.W19, U2.6, U2.12, U2.28, U2.41, U2.46, U2.52, U2.54, U3.2, U4.2, U5.2, U6.3, U6.13, U6.21, U7.4, U8.6, U8.7, U8.8, U8.9, U8.10, U8.11, U8.13, U8.14, U8.16, U8.22, U8.29, U9.1, U9.15, U9.38, U10.4, U11.1, US1.5, US1.6, US2.5, US2.6, Y1.2
GP0: J1.6, U1.B11
GP1: J1.8, U1.A10
GP2: J1.10, U1.A9
GP3: J1.12, U1.B9
GP4: J1.14, U1.A7
GP5: J1.16, U1.C8
GP6: J1.18, U1.C6
GP7: J1.24, U1.A6
GP8: J1.26, U1.A4
GP9: J1.28, U1.A2
GP10: J1.30, U1.C4
GP11: J1.32, U1.F4
GP12: J1.34, U1.G3, U9.9
GP13: J1.36, U1.H4, U9.4
GP14: J2.6, U1.U18, U8.27
GP15: J2.8, U1.N17, U8.1
GP16: J2.10, U1.N16, U8.3
GP17: J2.12, U1.L16, U8.5
GP18: J2.14, U1.H18
GP19: J2.16, U1.F17
GP20: J2.18, U1.D18
GP21: J2.24, U1.C18
GP22: J2.26, U1.B15
GP23: J2.28, U1.B17
GP24: J2.30, U1.C16
GP25: J2.32, U1.D14
GP26: J2.34, U1.B13
GP27: J2.36, U1.D13
GPDI_SCL: GPDI1.15, R25.2, U11.6
GPDI_SDA: GPDI1.16, R26.2, U11.5
JTAG_TCK: J4.4, U1.T5, U6.4, U9.30
JTAG_TDI: J4.3, U1.R5, U6.2, U9.37
JTAG_TDO: J4.6, U1.V4, U6.6, U9.6
JTAG_TMS: D22.1, J4.5, U1.U5, U6.5, U9.29
LED0: R41.1, U1.B2
LED1: R42.1, U1.C2
LED2: R43.1, U1.C1
LED3: R44.1, U1.D2
LED4: R45.1, U1.D1
LED5: R46.1, U1.E2
LED6: R47.1, U1.E1
LED7: R48.1, U1.H3
unnamed: D23.2, R63.1
unnamed: D24.1, R40.1
unnamed: D25.2, R64.1
unnamed: D26.1, R54.2
unnamed: D27.2, R66.2
OLED_BL: C63.1, LCD1.8, U1.J4
OLED_CLK: C68.2, LCD1.3, U1.P4
OLED_CS: C64.2, LCD1.7, U1.N2
OLED_DC: C65.1, LCD1.6, U1.P1
OLED_MOSI: C67.1, LCD1.4, U1.P3
OLED_RES: C66.2, LCD1.5, U1.P2
PWRBTn: B0.1, C60.1, D16.1, D17.1, D28.1, R3.2
SDRAM_A0: U1.M20, U2.23
SDRAM_A1: U1.M19, U2.24
SDRAM_A2: U1.L20, U2.25
SDRAM_A3: U1.L19, U2.26
SDRAM_A4: U1.K20, U2.29
SDRAM_A5: U1.K19, U2.30
SDRAM_A6: U1.K18, U2.31
SDRAM_A7: U1.J20, U2.32
SDRAM_A8: U1.J19, U2.33
SDRAM_A9: U1.H20, U2.34
SDRAM_A10: U1.N19, U2.22
SDRAM_A11: U1.G20, U2.35
SDRAM_A12: U1.G19, U2.36
SDRAM_BA0: U1.P19, U2.20
SDRAM_BA1: U1.N20, U2.21
SDRAM_CKE: U1.F20, U2.37
SDRAM_CLK: U1.F19, U2.38
SDRAM_D0: U1.J16, U2.2
SDRAM_D1: U1.L18, U2.4
SDRAM_D2: U1.M18, U2.5
SDRAM_D3: U1.N18, U2.7
SDRAM_D4: U1.P18, U2.8
SDRAM_D5: U1.T18, U2.10
SDRAM_D6: U1.T17, U2.11
SDRAM_D7: U1.U20, U2.13
SDRAM_D8: U1.E19, U2.42
SDRAM_D9: U1.D20, U2.44
SDRAM_D10: U1.D19, U2.45
SDRAM_D11: U1.C20, U2.47
SDRAM_D12: U1.E18, U2.48
SDRAM_D13: U1.F18, U2.50
SDRAM_D14: U1.J18, U2.51
SDRAM_D15: U1.J17, U2.53
SDRAM_DQM0: U1.U19, U2.15
SDRAM_DQM1: U1.E20, U2.39
SDRAM_nCAS: U1.T19, U2.17
SDRAM_nCS: U1.P20, U2.19
SDRAM_nRAS: U1.R20, U2.18
SDRAM_nWE: U1.T20, U2.16
SD_CLK: SD1.5, U1.H2, U9.13
SD_CMD: SD1.3, U1.J1, U9.23
SD_D0: SD1.7, U1.J3, U9.24
SD_D1: SD1.8, U1.H1, U9.26
SD_D2: SD1.1, U1.K1, U9.14
SD_D3: SD1.2, U1.K2, U9.16
SHUTDOWN: D15.2, R13.1, U1.G16
SW1: SW1.8, U1.E8
SW2: SW1.7, U1.D8
SW3: SW1.6, U1.D7
SW4: SW1.5, U1.E7
US2_ID: R66.1, US2.4
USB5V: D8.2, U6.12, US1.1
USB_FPGA_D+: D20.1, R40.2, R53.1, R63.2, U1.D15, U1.E16
USB_FPGA_D-: D21.1, R52.1, R54.1, R64.2, U1.E15, U1.F16
USB_FPGA_PULL_D+: D23.1, D24.2, U1.B12
USB_FPGA_PULL_D-: D25.1, D26.2, U1.C12
USB_FTDI_D+: R50.1, U6.8
USB_FTDI_D-: R49.1, U6.9
USER_PROGRAMN: D29.1, U1.M4
WIFI_EN: R34.2, R35.1, U1.J5
WIFI_GPIO0: R56.2, U1.F1, U9.25
WIFI_GPIO19: U1.N4, U9.31
WIFI_GPIO21: U1.K5, U9.33
WIFI_GPIO22: U1.L2, U9.36
WIFI_GPIO25: U1.E9, U9.10
WIFI_GPIO26: U1.L1, U9.11
WIFI_GPIO27: U1.N3, U9.12
WIFI_GPIO35: U1.E6, U9.7
WIFI_RXD: U1.K3, U9.34
WIFI_TXD: U1.K4, U9.35
nRESET: R9.1, U6.11
